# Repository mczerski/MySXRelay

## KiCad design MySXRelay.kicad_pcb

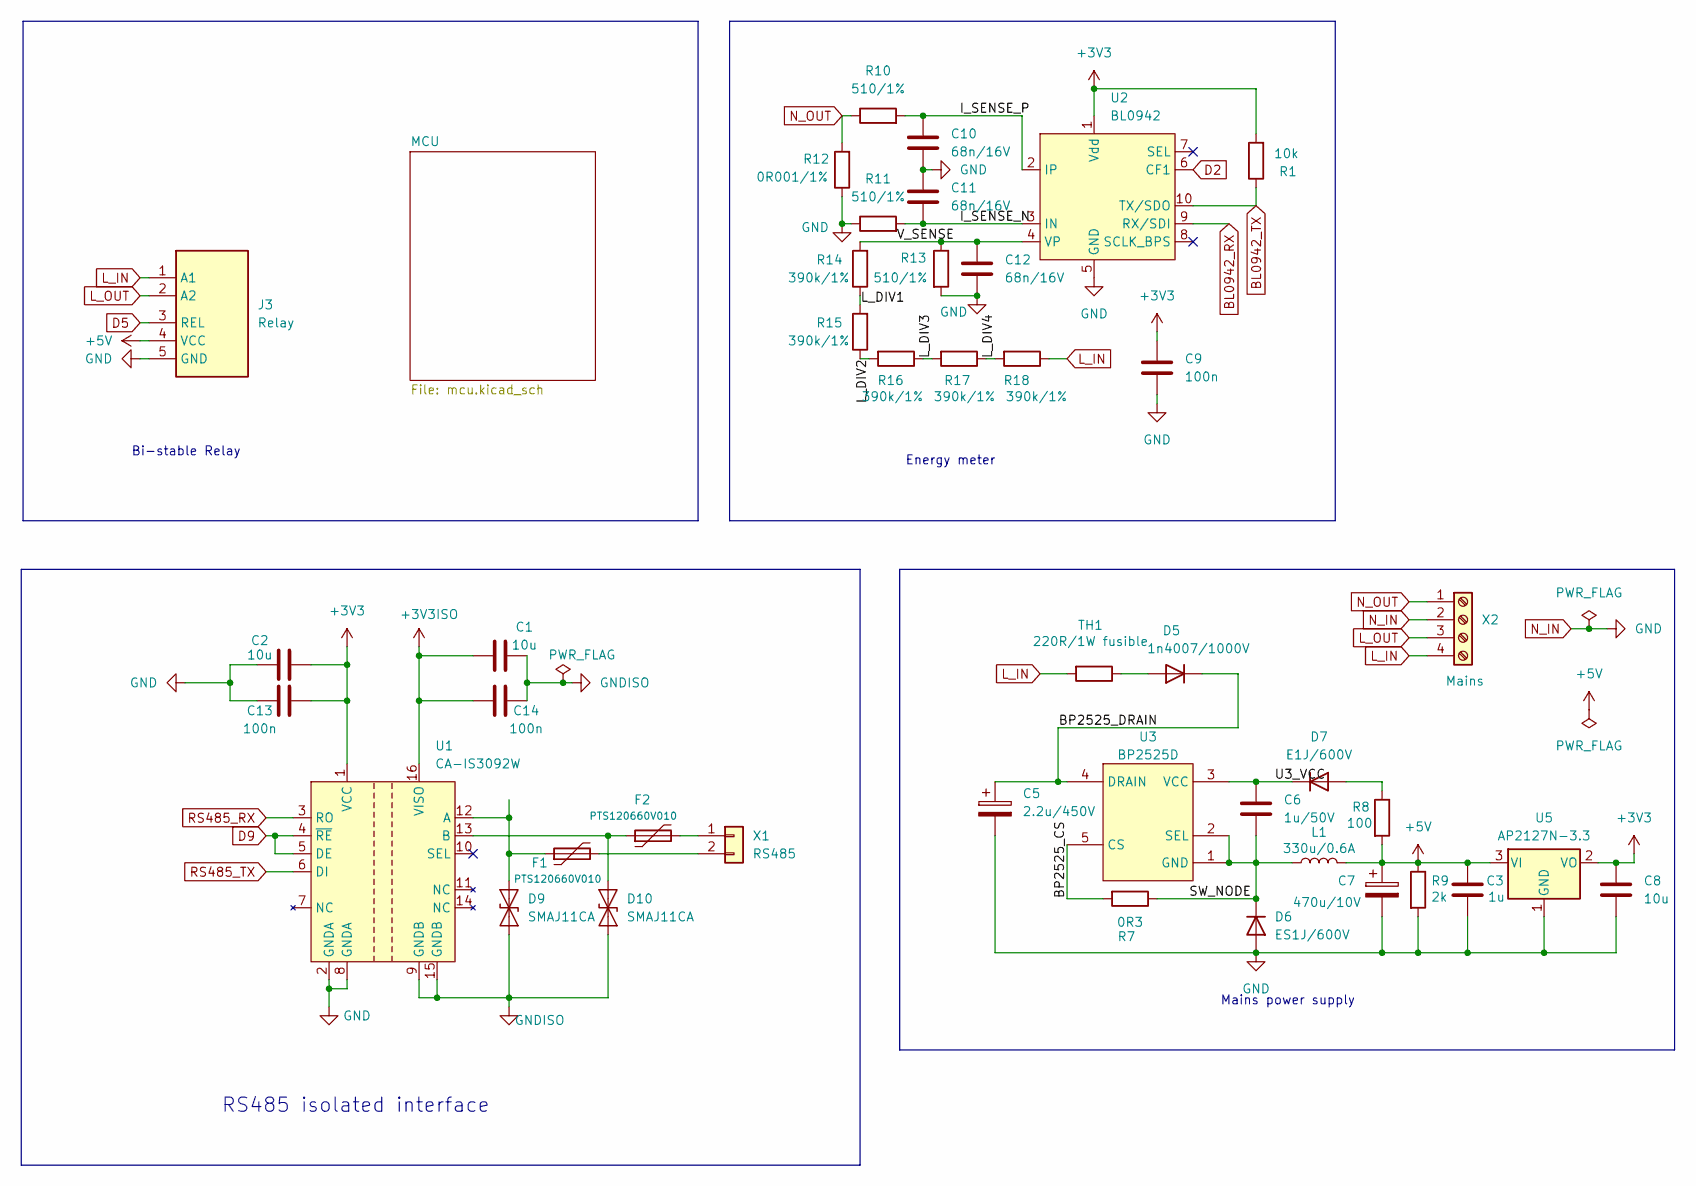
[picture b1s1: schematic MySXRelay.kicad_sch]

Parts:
C1, C2, C8: 10u; C_0603_1608Metric
C3: 1u; C_0603_1608Metric
C5: 2.2u/450V; CP_Radial_D8.0mm_P3.50mm
C6: 1u/50V; C_0603_1608Metric
C7: 470u/10V; CP_Radial_D8.0mm_P3.50mm
C9, C13, C14: 100n; C_0402_1005Metric
C10, C11, C12: 68n/16V; C_0603_1608Metric
D5: 1n4007/1000V; D_SOD-123F
D6: ES1J/600V; D_SOD-123F
D7: E1J/600V; D_SOD-123F
D9, D10: SMAJ11CA; D_SMA
F1, F2: PTS120660V010; Fuse_1206_3216Metric_Pad1.42x1.75mm_HandSolder
J3: Relay; edge_connector
L1: 330u/0.6A; L_Radial_D7.5mm_P3.00mm_Ferrocore_COIL0608
R1: 10k; R_0603_1608Metric
R7: 0R3; R_1206_3216Metric
R8: 100; R_0603_1608Metric
R9: 2k; R_0603_1608Metric
R10, R11, R13: 510/1%; R_0603_1608Metric
R12: 0R001/1%; R_2512_6332Metric_Pad1.40x3.35mm_HandSolder
R14, R15, R16, R17, R18: 390k/1%; R_1206_3216Metric
TH1: 220R/1W fusible; R_Axial_DIN0207_L6.3mm_D2.5mm_P5.08mm_Vertical
U1: CA-IS3092W; SOIC-16W_7.5x10.3mm_P1.27mm
U2: BL0942
U3: BP2525D; SOT-33-5A
U5: AP2127N-3.3; SOT-23
X1: RS485; JST-XH_S_2P-2.54MM
X2: Mains; TerminalBlock_Phoenix_MKDS-1,5-4-5.08_1x04_P5.08mm_Horizont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

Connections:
+3V3: C2.2, C8.1, C9.1, C13.2, R1.2, U1.1 (VCC), U2.1 (Vdd), U5.2 (VO); also elsewhere on the board
+3V3ISO: C1.1, C14.1, U1.16 (VISO)
+5V: C3.1, C7.1, J3.4 (VCC), L1.2, R8.2, R9.1, U5.3 (VI)
/BP2525_CS: R7.2, U3.5 (CS)
/BP2525_DRAIN: C5.1, D5.1 (K), U3.4 (DRAIN)
/I_SENSE_N: C11.2, R11.2, U2.3 (IN)
/I_SENSE_P: C10.1, R10.2, U2.2 (IP)
/L_DIV1: R14.1, R15.2
/L_DIV2: R15.1, R16.2
/L_DIV3: R16.1, R17.2
/L_DIV4: R17.1, R18.2
/SW_NODE: C6.2, D6.1 (K), L1.1, R7.1, U3.1 (GND), U3.2 (SEL)
/U3_VCC: C6.1, D7.1 (K), U3.3 (VCC)
/V_SENSE: C12.1, R13.1, R14.2, U2.4 (VP)
BL0942_RX: U2.9 (RX/SDI); also elsewhere on the board
BL0942_TX: R1.1, U2.10 (TX/SDO); also elsewhere on the board
D2: U2.6 (CF1); also elsewhere on the board
D5: J3.3 (REL); also elsewhere on the board
D9: U1.4 (~RE), U1.5 (DE); also elsewhere on the board
GNDISO: C1.2, C14.2, D9.1 (A1), D10.1 (A1), U1.9 (GNDB), U1.15 (GNDB)
L_IN: J3.1 (A1), R18.1, TH1.2, X2.4
L_OUT: J3.2 (A2), X2.3
N_IN: C2.1, C3.2, C5.2, C7.2, C8.2, C9.2, C10.2, C11.1, C12.2, C13.1, D6.2 (A), J3.5 (GND), R9.2, R11.1, R12.1, R13.2, U1.2 (GNDA), U1.8 (GNDA), U2.5 (GND), U5.1 (GND), X2.2; also elsewhere on the board
N_OUT: R10.1, R12.2, X2.1
unnamed: D5.2 (A), TH1.1
unnamed: D7.2 (A), R8.1
unnamed: D9.2 (A2), F1.1, U1.12 (A)
unnamed: D10.2 (A2), F2.1, U1.13 (B)
unnamed: F2.2, X1.1
unnamed: F1.2, X1.2
RS485_RX: U1.3 (RO); also elsewhere on the board
RS485_TX: U1.6 (DI); also elsewhere on the board

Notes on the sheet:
RS485 isolated interface
Mains power supply
Energy meter
Bi-stable Relay

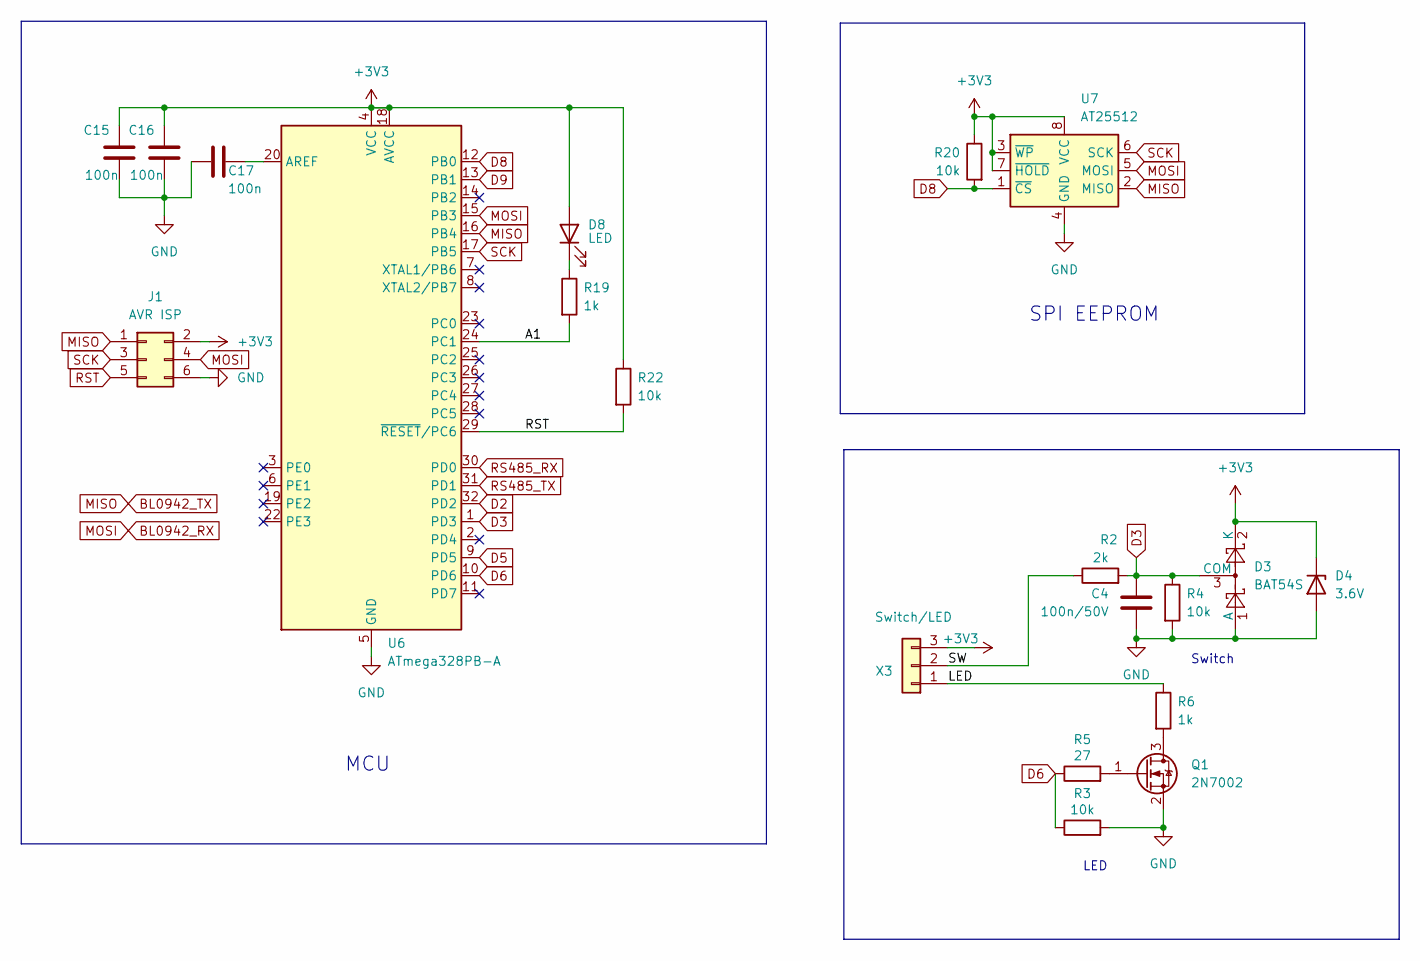
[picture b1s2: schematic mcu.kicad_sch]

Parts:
C4: 100n/50V; C_0402_1005Metric
C15, C16, C17: 100n; C_0402_1005Metric
D3: BAT54S; SOT-23
D4: 3.6V; D_MiniMELF
D8: LED; LED_0805_2012Metric_Pad1.15x1.40mm_HandSolder
J1: AVR ISP; PinHeader_2x03_P2.54mm_Vertical
Q1: 2N7002; SOT-23
R2: 2k; R_0603_1608Metric
R3, R4, R20, R22: 10k; R_0603_1608Metric
R5: 27; R_0603_1608Metric
R6, R19: 1k; R_0603_1608Metric
U6: ATmega328PB-A; TQFP-32_7x7mm_P0.8mm
U7: AT25512; SOIC-8_3.9x4.9mm_P1.27mm
X3: Switch/LED; JST-XH_S_3P-2.54MM

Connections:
+3V3: C15.1, C16.1, D3.2 (K), D4.1 (K), D8.2 (A), J1.2, R20.1, R22.1, U6.4 (VCC), U6.18 (AVCC), U7.3 (~WP), U7.7 (~HOLD), U7.8 (VCC), X3.3; also elsewhere on the board
/MCU/A1: R19.2, U6.24 (PC1)
/MCU/LED: R6.1, X3.1
/MCU/SW: R2.1, X3.2
BL0942_RX: J1.4, U6.15 (PB3), U7.5 (MOSI); also elsewhere on the board
BL0942_TX: J1.1, U6.16 (PB4), U7.2 (MISO); also elsewhere on the board
D2: U6.32 (PD2); also elsewhere on the board
D3: C4.1, D3.3 (COM), R2.2, R4.1, U6.1 (PD3)
D5: U6.9 (PD5); also elsewhere on the board
D6: R3.1, R5.1, U6.10 (PD6)
D8: R20.2, U6.12 (PB0), U7.1 (~CS)
D9: U6.13 (PB1); also elsewhere on the board
N_IN: C4.2, C15.2, C16.2, C17.2, D3.1 (A), D4.2 (A), J1.6, Q1.2 (S), R3.2, R4.2, U6.5 (GND), U6.21 (GND), U7.4 (GND); also elsewhere on the board
unnamed: D8.1 (K), R19.1
unnamed: Q1.3 (D), R6.2
unnamed: Q1.1 (G), R5.2
unnamed: C17.1, U6.20 (AREF)
RS485_RX: U6.30 (PD0); also elsewhere on the board
RS485_TX: U6.31 (PD1); also elsewhere on the board
RST: J1.5, R22.2, U6.29 (~RESET/PC6)
SCK: J1.3, U6.17 (PB5), U7.6 (SCK)

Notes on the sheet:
Switch
SPI EEPROM
LED
MCU

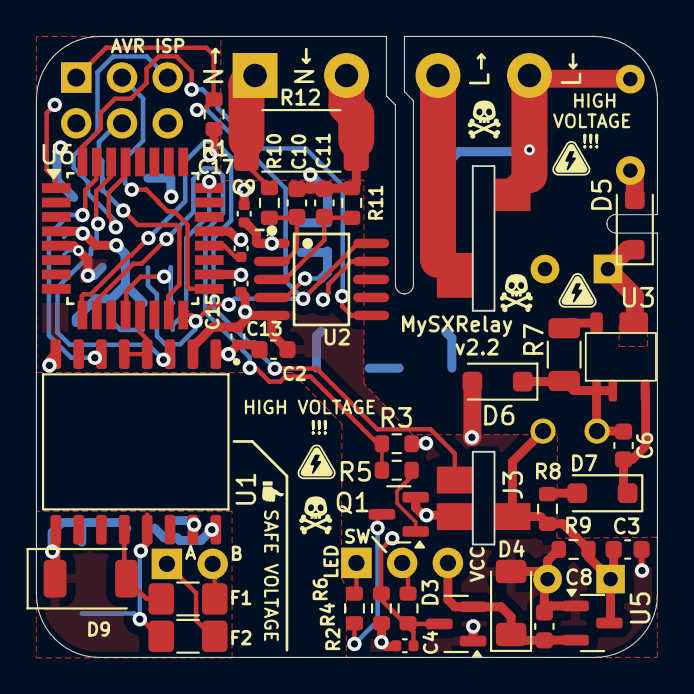
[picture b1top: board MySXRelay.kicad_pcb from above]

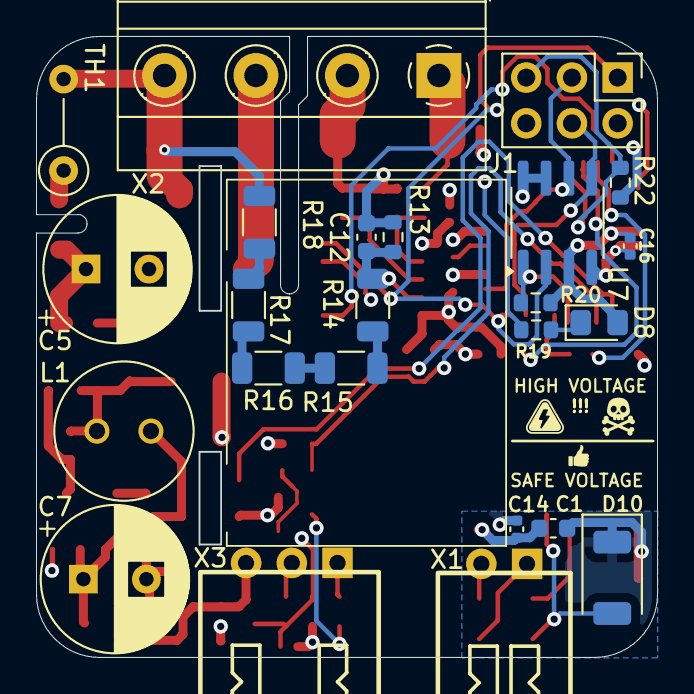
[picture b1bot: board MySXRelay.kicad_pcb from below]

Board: 4 copper layers, 34.5 x 34.5 mm, 62 parts (24 on the bottom side), 44 nets.

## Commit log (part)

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2024-10-12 initiall schematic
2024-10-14 finished schematic
2024-10-16 add LDO on mains power supply output
2024-10-16 setup PCS dimensions
2024-10-28 PCB WIP
2024-10-28 WIP PCB
2024-11-03 PCB placment and routing finished
2024-11-03 version 1.0
2024-11-24 update schematic to new version
    - include MCU, remove MySXMotherboard
    - only RS485 interface is isolated
2024-11-25 update pcb (WIP)
2024-11-26 relay module updated
2024-11-26 finished PCB
2024-12-04 changed mains connector
2024-12-06 finish PCB afterr changing connector
2024-12-13 change AP2204 to AP2202
2024-12-13 remove BL0942 TX pin jumper and add pull up resistor
2024-12-16 change RS485 interface LDO package to sot-89
2024-12-16 add BOM + update schematic parts descriptions
2024-12-24 shrink PCB to fit 40mmx40mm HM-1551V1WH case
2024-12-24 add png snapshots
2024-12-25 add high voltage cutouts
2025-01-11 fix part numbers positions on silcscreen
2025-01-14 move vias out of pads and cover vies with soldermask
